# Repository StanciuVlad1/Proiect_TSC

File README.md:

## Stanciu Vlad-Mihai
#### 331CC
<br><br>

OpenBook este un proiect open-source care urmărește să aducă lectura digitală mai aproape de oricine, printr-un dispozitiv accesibil și ușor de reprodus. În cadrul acestui start-up, dezvoltăm un eBook Reader minimalist, construit pe platforma ESP32-C6, echipat cu un ecran e-paper de 7.5 inch, baterie Li-Po, încărcare prin USB-C și butoane fizice pentru navigare.

Dispozitivul este conceput să fie eficient din punct de vedere energetic și intuitiv în utilizare, oferind o interfață simplă bazată pe GPIO, optimizată pentru afișarea de texte și o experiență de e-reading plăcută.

## Cuprins

- [Prezentare Proiect](#prezentare-proiect)
- [Diagramă Bloc](#diagrama-bloc)
- [Lista de Materiale (BOM)](#lista-de-materiale-bom)
- [Funcționalitate Hardware](#functionalitate-hardware)
- [Alocarea Pinilor ESP32-C6](#alocarea-pinilor-esp32-c6)
- [Note de Design](#note-de-design)

## Prezentare Proiect

OpenBook este un cititor de e-bookuri open-source bazat pe microcontrolerul ESP32-C6. Dispozitivul include un display e-paper, stocare pe card SD pentru e-bookuri, o interfață USB-C pentru alimentare și date, și un design compact care se potrivește într-o carcasă personalizată. Scopul este crearea unui e-reader ieftin, modificabil, care poate fi produs în masă, respectând principiile open-source.

Acest repository conține:

- **Hardware**: Fișiere pentru schemă electrică și PCB.
- **Manufacturing**: Fișiere Gerber, Lista de Materiale (BOM) și fișiere Pick and Place.
- **Mechanical**: Modele 3D ale dispozitivului complet (PCB, baterie, display și carcasă).
- **Images**: Randări ale PCB-ului și dispozitivului.

## 🗂️ Diagrama bloc

## Lista de Materiale (BOM)

Tabelul următor listează componentele folosite în designul OpenBook, cu link-uri către furnizori și datasheet-uri.

| Componentă                | Număr Piesă                  | Cantitate | Link Furnizor                                                                 | Link Datasheet                                                                                                                                              | Note                              |
|---------------------------|------------------------------|-----------|--------------------------------------------------------------------------------|-------------------------------------------------------------------------------------------------------------------------------------------------------------|-----------------------------------|
| Senzor mediu              | BME680                       | 1         | [SnapEDA](https://www.snapeda.com/parts/BME680/Bosch/view-part/?welcome=home)   | [Bosch](https://www.bosch-sensortec.com/media/boschsensortec/downloads/datasheets/bst-bme680-ds001.pdf)                                                     | Senzor temperatură, umiditate     |
| Buton tactil              | EVQPUJ02K                    | 3         | [Panasonic](https://industry.panasonic.com/global/en/products/control/switch/light-touch/number/evqpuj02k) | [LCSC](https://www.lcsc.com/datasheet/lcsc_datasheet_2201121800_PANASONIC-EVQPUJ02K_C2936858.pdf)                              | Butoane navigare și pornire       |
| Condensator               | R0402 100K                   | [TBD]     | [ComponentSearch](https://componentsearchengine.com/part-view/R0402%201%25%20100%20K%20(RC0402FR-07100KL)/YAGEO) | [Resistor](https://www.resistor.com/assets/pdf/0402tstd.pdf)                                                                 | Condensator decuplare, SMD 0402   |
| Rezistor                  | R0402 100K                   | [TBD]     | [ComponentSearch](https://componentsearchengine.com/part-view/R0402%201%25%20100%20K%20(RC0402FR-07100KL)/YAGEO) | [Resistor](https://www.resistor.com/assets/pdf/0402tstd.pdf)                                                                 | Rezistor, SMD 0402                |
| Baterie                   | CPH3225A                     | 1         | [SnapEDA](https://www.snapeda.com/parts/CPH3225A/Seiko+Instruments/view-part/?ref=eda) | [Octopart](https://octopart.com/datasheet/cph3225a-seiko-25340571)                                                                  | Baterie Li-Po, ~500mAh            |
| LED                       | KP-1608SURCK                 | 1         | [SnapEDA](https://www.snapeda.com/parts/KP-1608SURCK/Kingbright/view-part/?ref=search&t=LED%200603) | [ELV](https://media.elv.com/file/107153_led_surck1608_data.pdf)                                                                     | LED 0603, indicator               |
| Protecție ESD             | USBLC6-2SC6Y                 | 1         | [SnapEDA](https://www.snapeda.com/parts/USBLC6-2SC6Y/STMicroelectronics/view-part/?ref=eda) | [DigiKey](https://www.digikey.com/en/htmldatasheets/production/1375342/0/0/1/usblc6-2sc6y)                                          | Protecție USB                     |
| Diodă Schottky            | SD0805S020S1R0               | 1         | [Mouser](https://ro.mouser.com/ProductDetail/KYOCERA-AVX/SD0805S020S1R0?qs=jCA%252BPfw4LHbpkAoSnwrdjw%3D%3D) | [AllDataSheet](https://www.alldatasheet.com/view.jsp?Searchword=SD0805S&sField=2)                                                    | Diodă pentru alimentare           |
| Supresor ESD              | PGB1010603MR                | 1         | [SnapEDA](https://www.snapeda.com/parts/PGB1010603MR/Littelfuse/view-part/?ref=eda) | [AllDataSheet](https://www.alldatasheet.com/view.jsp?Searchword=Pgb1010603mr)                                                        | Protecție ESD                     |
| Detector tensiune         | BD5229G-TR                   | 1         | [ComponentSearch](https://componentsearchengine.com/part-view/BD5229G-TR/ROHM%20Semiconductor) | [LCSC](https://www.lcsc.com/datasheet/lcsc_datasheet_2201131330_ROHM-Semicon-BD5229G-TR_C962636.pdf)                         | Monitorizare tensiune             |
| Regulator tensiune        | XC6220A331MR-G               | 1         | [ComponentSearch](https://componentsearchengine.com/part-view/XC6220A331MR-G/Torex) | [AllDataSheet](https://www.alldatasheet.com/view.jsp?Searchword=Xc6220)                                                              | Regulator 3.3V                    |
| Conector USB-C            | USB4110-GF-A                 | 1         | [ComponentSearch](https://componentsearchengine.com/part-view/USB4110-GF-A/GCT%20(GLOBAL%20CONNECTOR%20TECHNOLOGY)) | [GCT](https://gct.co/files/drawings/usb4110.pdf)                                                                            | Interfață USB-C                   |
| LED                       | LEDCHIP-LED0603              | 1         | [Mouser](https://eu.mouser.com/ProductDetail/Adafruit/4208?qs=PzGy0jfpSMtbScLbr0L5dw%3D%3D) | [Arrow](https://www.arrow.com/en/manufacturers/adafruit-industries/datasheets)                                              | LED 0603, Adafruit                |
| Bobină                    | [TBD]                        | 1         | [Comet](https://store.comet.srl.ro/Catalogue/Product/43497/)                           | [Scribd](https://www.scribd.com/document/814581278/Datasheet-Bobina)                                                                | Inductor pentru alimentare        |
| Siguranță resetabilă      | PFMF                          | 1         | [Mouser](https://www.mouser.co.uk/ProductDetail/EPCOS-TDK/B72520T0350K062?qs=dEfas%2FXlABIszF52uu7vrg%3D%3D) | [Mouser](https://ro.mouser.com/c/ds/circuit-protection/thermistors/resettable-fuses-pptc/?m=Schurter&series=PFMF)             | Protecție circuit                 |
| MOSFET                    | DMG2305UX-7                  | 1         | [ComponentSearch](https://componentsearchengine.com/part-view/DMG2305UX-7/Diodes%20Incorporated) | [Mouser](https://www.mouser.com/datasheet/2/115/DMG2305UX-266242.pdf)                                                       | Comutare putere                   |
| MOSFET                    | Si1308EDL-T1-GE3             | 1         | [ComponentSearch](https://componentsearchengine.com/part-view/SI1308EDL-T1-GE3/Vishay) | [AllDataSheet](https://www.alldatasheet.com/view.jsp?Searchword=Si1308edl)                                                   | Comutare putere                   |
| IC management baterie     | MCP73831T-5ACI/OT            | 1         | [Mouser](https://www.mouser.co.uk/ProductDetail/Microchip-Technology/MCP73831T-5ACI-OT?qs=hH%252BOa0VZEiAcgAcEkuamXg%3D%3D) | [Microchip](https://ww1.microchip.com/downloads/en/DeviceDoc/MCP73831-Family-Data-Sheet-DS20001984H.pdf)                     | Încărcare baterie                 |
| Lipire SMD                | SMD Solder                   | [TBD]     | [GrabCAD](https://grabcad.com/library/solder-jumpers-1)                                | -                                                                                                                                                           | Pentru asamblare SMD              |
| Memorie flash             | W25Q512JVEIQ                 | 1         | [SnapEDA](https://www.snapeda.com/parts/W25Q512JVEIQ/Winbond+Electronics/view-part/) | [Mouser](https://www.mouser.com/datasheet/2/949/W25Q512JV_SPI_RevB_06252019_KMS-2487502.pdf)                                | Memorie SPI                       |
| Modul microcontroler      | ESP32-C6-WROOM-1-N8          | 1         | [SnapEDA](https://www.snapeda.com/parts/ESP32-C6-WROOM-1-N8/Espressif+Systems/view-part/?ref=eda) | [Mouser](https://www.mouser.com/catalog/specsheets/Espressif_ESP32_C6_WROOM_1%20_Datasheet_V0.1_PRELIMINARY_en.pdf)         | Modul Wi-Fi/Bluetooth             |
| Ceas timp real            | DS3231SN#                    | 1         | [SnapEDA](https://www.snapeda.com/parts/DS3231SN%23/Analog+Devices/view-part/?ref=eda) | [AllDataSheet](https://www.alldatasheet.com/view.jsp?Searchword=Ds3231sn%20datasheet)                                        | RTC pentru timp                   |
| Monitor baterie           | MAX17048G+T10                | 1         | [SnapEDA](https://www.snapeda.com/parts/MAX17048G+T10/Analog+Devices/view-part/?ref=eda) | [AllDataSheet](https://www.alldatasheet.com/view.jsp?Searchword=Max17048)                                                    | Monitorizare nivel baterie        |

## Funcționalitate Hardware

Hardware-ul OpenBook este proiectat pentru a echilibra costul, eficiența energetică și funcționalitatea. Caracteristicile principale includ:

- **Microcontroler ESP32-C6**:
  - **Nucleu**: Procesor RISC-V single-core.
  - **Conectivitate**: Wi-Fi 6 și Bluetooth 5 pentru actualizări de firmware sau integrare cloud.
  - **Interfețe**: SPI pentru display și card SD, GPIO pentru butoane, USB pentru alimentare și depanare.
  - **Consum de energie**: Optimizat pentru funcționare cu consum redus, cu moduri de sleep pentru a prelungi durata bateriei.

- **Display E-Paper**:
  - Display e-paper de 2.13" (rezoluție [TBD, ex. 250x122 pixeli]).
  - Conectat prin SPI pentru actualizare rapidă și consum redus.
  - Ideal pentru citit în diverse condiții de iluminare, cu consum minim.

- **Modul Card SD**:
  - Stochează e-bookuri și alte fișiere media.
  - Conectat prin SPI pentru transfer de date fiabil.
  - Suportă carduri microSD standard.

- **Interfață USB-C**:
  - Furnizează alimentare (intrare 5V) și încarcă bateria prin IC-ul de management al puterii.
  - Suportă transfer de date pentru depanare sau actualizări de firmware.

- **Baterie și Management Putere**:
  - Baterie Li-Po de 3.7V (~500mAh, capacitate exactă [TBD]).
  - IC de management al puterii (ex. TP4056) gestionează încărcarea și reglarea tensiunii (3.3V pentru ESP32 și alte componente).
  - Durata estimată a bateriei: [TBD, ex. 20 ore de citire activă], bazată pe calcule pentru actualizarea display-ului, modurile sleep ale ESP32 și accesul la cardul SD.

- **Butoane**:
  - Trei butoane tactile pentru navigare (următoarea/pagina anterioară) și pornire/meniu.
  - Conectate la pinii GPIO ai ESP32 cu rezistoare pull-up.

- **Calcule Consum Energie**:
  - ESP32-C6 (activ): ~100mA la 3.3V.
  - Display E-Paper (actualizare): ~10mA pentru 1s per pagină.
  - Card SD (citire): ~50mA în timpul accesului.
  - Consum total activ: [TBD, ex. ~150mA mediu].
  - Mod sleep: [TBD, ex. <1mA].

*(Notă: Actualizează consumul de energie și alte specificații pe baza alegerilor tale de design și a datasheet-urilor.)*

## Alocarea Pinilor ESP32-C6

Pinii ESP32-C6 sunt alocați astfel:

| Pin       | Funcție                 | Componentă/Modul        | Note                              |
|-----------|-------------------------|-------------------------|-----------------------------------|
| GPIO0     | SPI MOSI                | Display E-Paper, Card SD| Bus SPI comun                     |
| GPIO1     | SPI MISO                | Display E-Paper, Card SD| Bus SPI comun                     |
| GPIO2     | SPI SCK                 | Display E-Paper, Card SD| Bus SPI comun                     |
| GPIO3     | SPI CS (Display)        | Display E-Paper         | Selectare cip pentru display      |
| GPIO4     | SPI CS (Card SD)        | Modul Card SD           | Selectare cip pentru card SD      |
| GPIO5     | Buton 1 (Pagina Urm.)   | Buton Tactil            | Pull-up, activ low                |
| GPIO6     | Buton 2 (Pagina Ant.)   | Buton Tactil            | Pull-up, activ low                |
| GPIO7     | Buton 3 (Pornire/Meniu) | Buton Tactil            | Pull-up, activ low                |
| GPIO8     | Reset Display           | Display E-Paper         | Activ low                         |
| GPIO9     | Busy Display            | Display E-Paper         | Intrare de la display             |
| VBUS      | Alimentare USB          | Conector USB-C          | Intrare 5V                        |
| 3V3       | Linie Alimentare        | Toate componentele      | Reglat din baterie/USB            |

*(Notă: Verifică alocarea pinilor față de schemă. Actualizează tabelul cu numerele exacte ale pinilor și funcțiile pe baza designului tău.)*

### De ce acești pini?

- **Pini SPI (GPIO0-4)**: Aleși pentru suportul hardware dedicat SPI, asigurând comunicație rapidă și fiabilă cu display-ul și cardul SD. Un bus SPI comun minimizează utilizarea pinilor.
- **Pini Butoane (GPIO5-7)**: Selectați pentru capabilitățile de intrare generală și suport pentru întreruperi, permițând interacțiune rapidă cu utilizatorul.
- **Pini Control Display (GPIO8-9)**: Folosiți pentru semnalele de reset și busy, conform cerințelor datasheet-ului display-ului e-paper.
- **Pini Alimentare (VBUS, 3V3)**: Standard pentru livrarea și reglarea energiei.

## Note de Design

- **Schemă și Design PCB**:
  - Schema (`Hardware/openbook.sch`) respectă referința furnizată.
  - Layout-ul PCB (`Hardware/openbook.brd`) respectă constrângerile mecanice, cu toate componentele pe stratul TOP și rutarea pe ambele straturi TOP și BOTTOM.
  - Traseele de alimentare folosesc lățimea de 0.3mm, iar traseele de semnal au lățimea minimă de 0.15mm, conform ghidului.
  - Antena ESP32-C6 este poziționată la marginea PCB-ului, cu o decupare dedesubt pentru a minimiza interferențele.

- **Design Mecanic**:
  - Modelul 3D (`Mechanical/openbook.step`) include PCB-ul, bateria, display-ul e-paper și carcasa modificată.
  - Bateria se conectează direct la pad-uri de test (fără conector JST) pentru a economisi spațiu.

## 🔧 Provocări și decizii tehnice

- **Erori DRC**  
  Au fost ignorate erorile de tip *"Only INPUT pins on NET ID"* și cele legate de dimensiunile butoanelor și conectorului USB, în conformitate cu ghidul de proiectare, deoarece nu afectează funcționarea corectă a dispozitivului.

- **Amplasarea componentelor**  
  Componentele au fost plasate strategic în jurul ESP32 și al driverului e-paper pentru a reduce lungimea traseelor și a asigura o bună integritate a semnalului.

- **Via Stitching**  
  A fost implementat între planele de masă TOP și BOTTOM, în special în proximitatea ESP32, pentru a îmbunătăți performanța EMI și stabilitatea generală.

- **Silkscreen**  
  Au fost incluse doar denumirile componentelor, fără valorile acestora, pentru a păstra lizibilitatea și a respecta bunele practici în designul PCB-urilor.

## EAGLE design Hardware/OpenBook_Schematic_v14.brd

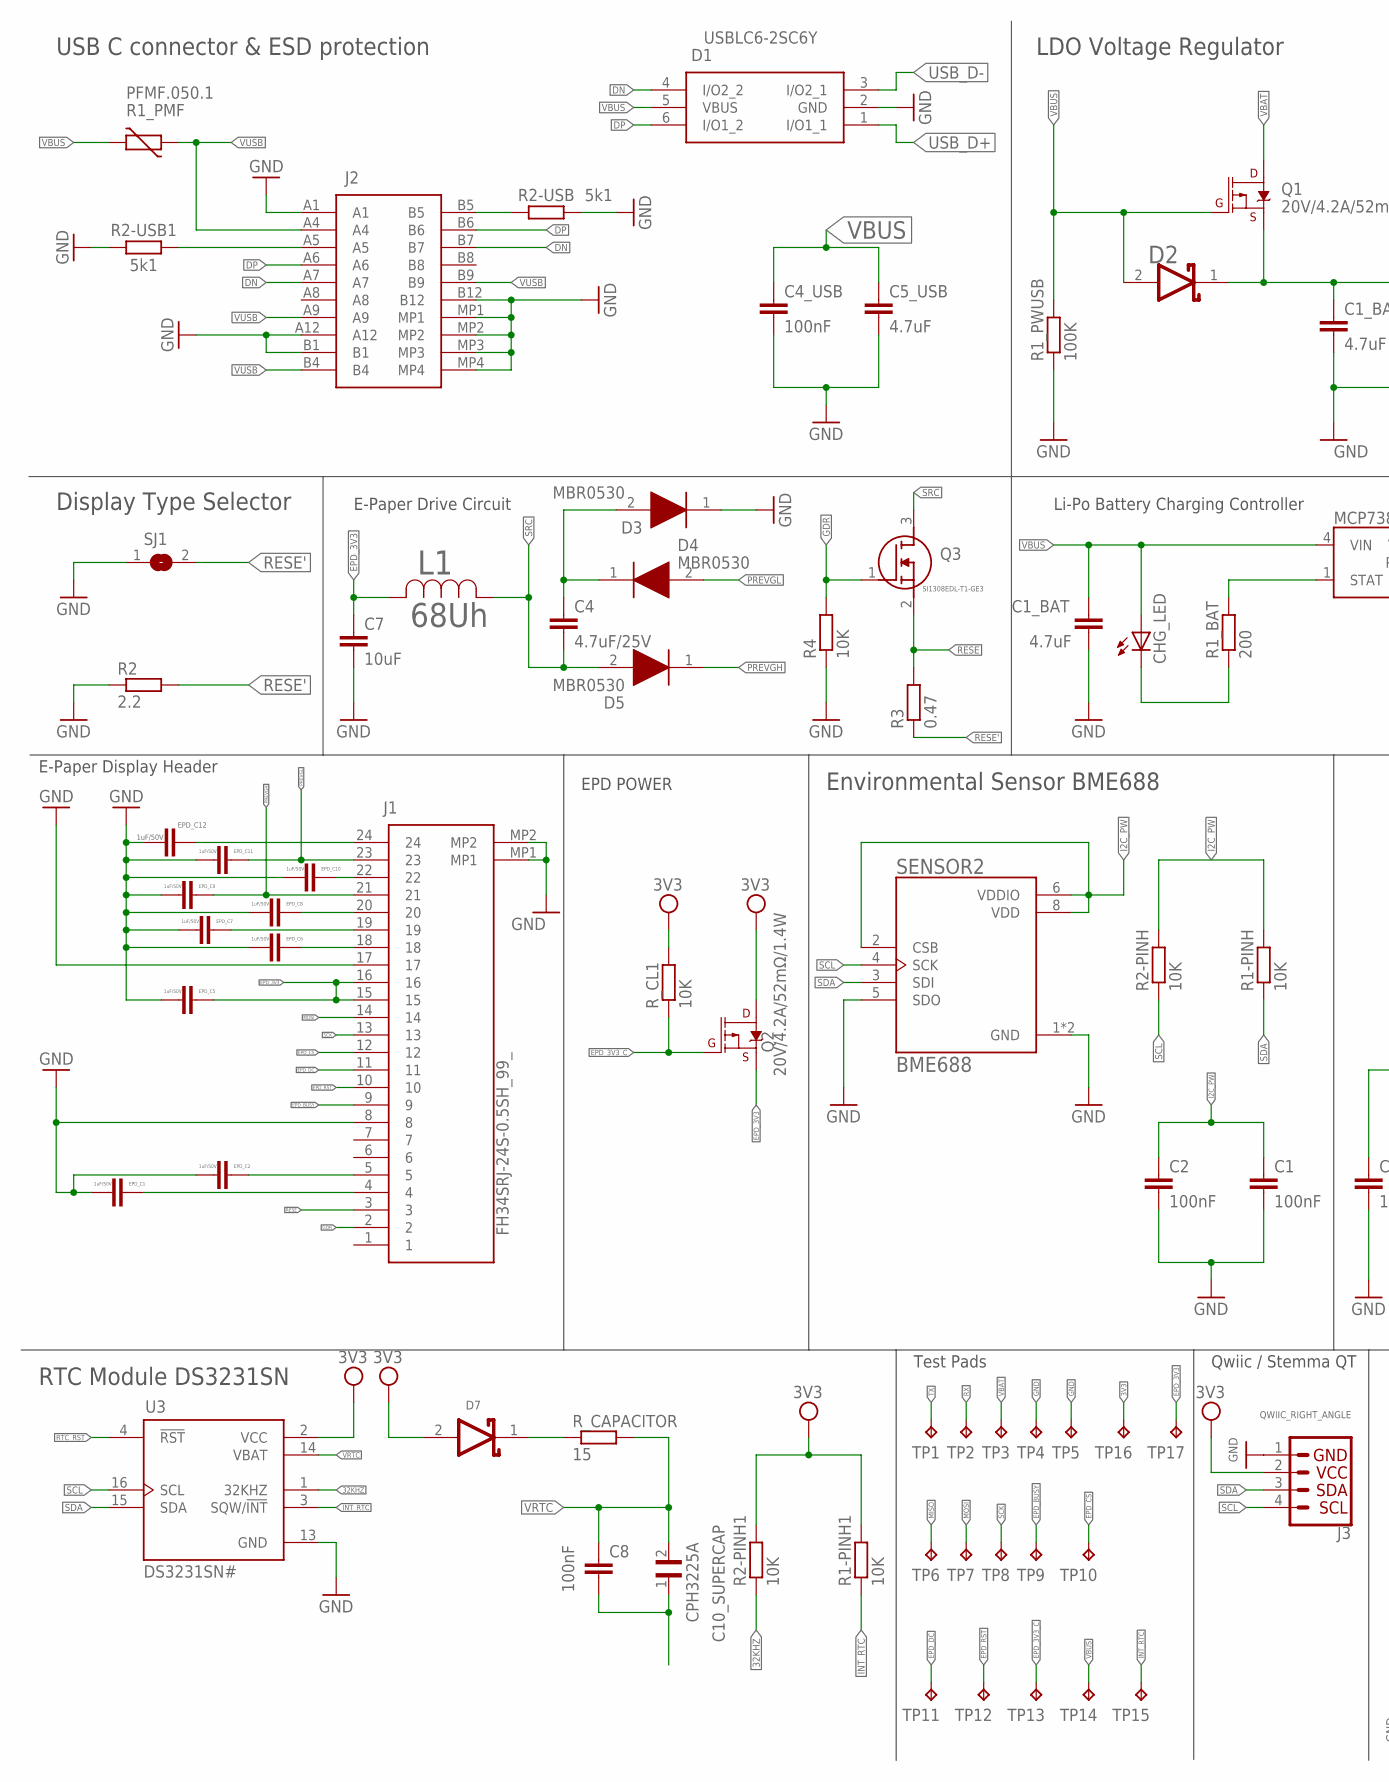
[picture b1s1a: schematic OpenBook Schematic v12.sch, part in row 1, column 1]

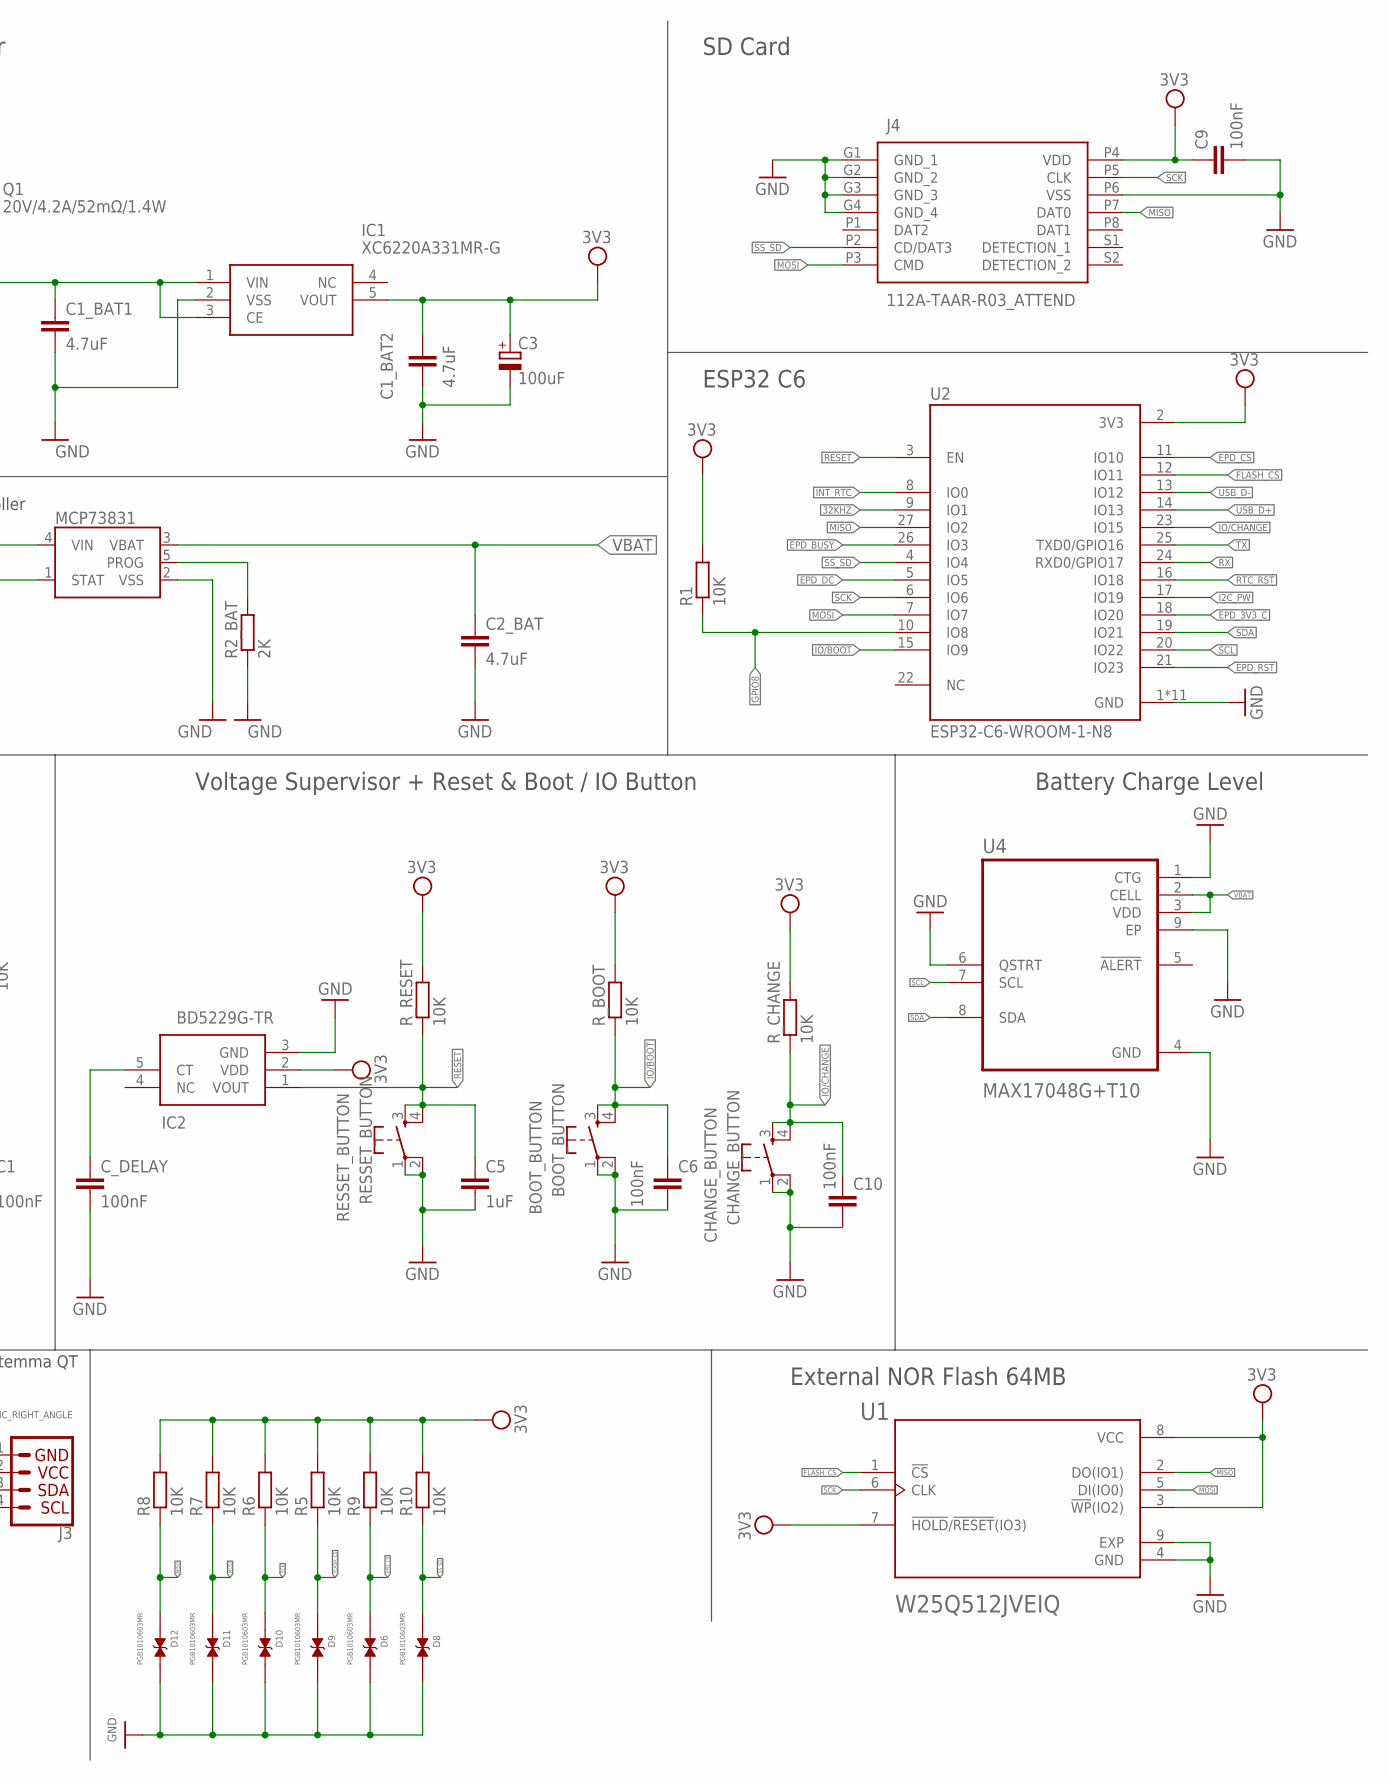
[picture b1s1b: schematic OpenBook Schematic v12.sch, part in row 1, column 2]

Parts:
BOOT_BUTTON: BOOT_BUTTON; MYBUTTON
C1, C2, C4_USB, C6, C8, C9, C10: 100nF; EAGLE-LTSPICE_C0402
C1_BAT, C1_BAT1, C1_BAT2, C2_BAT, C5_USB: 4.7uF; EAGLE-LTSPICE_C0402
C3: 100uF; RCL_CT3528
C4: 4.7uF/25V; EAGLE-LTSPICE_C0402
C5: 1uF; EAGLE-LTSPICE_C0402
C7: 10uF; EAGLE-LTSPICE_C0402
C10_SUPERCAP: CPH3225A; CAPCP3225X100N
CHANGE_BUTTON: CHANGE_BUTTON; MYBUTTON
CHG_LED: ADAFRUIT_LEDCHIP-LED0603; ADAFRUIT_CHIP-LED0603
C_DELAY: 100nF; EAGLE-LTSPICE_C0402
D1: USBLC6-2SC6Y; SOT95P280X145-6N
D2, D7: ESP32_WROVER_AVX---SD0805S020S1R0_AVX_SD0805S020S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; ESP32_WROVER_AVX---SD0805S020S1R0_AVX_SD0805S020S1R0_0
D3, D4, D5: MBR0530; SOD3716X135N
D6, D8, D9, D10, D11, D12: PGB1010603MR; DIOC1608X36N
EPD_C1, EPD_C2, EPD_C5, EPD_C6, EPD_C7, EPD_C8, EPD_C9, EPD_C10, EPD_C11, EPD_C12: 1uF/50V; EAGLE-LTSPICE_C0402
IC1: XC6220A331MR-G; SOT95P280X120-5N
IC2: BD5229G-TR; SOT95P280X125-5N
J1: FH34SRJ-24S-0.5SH_99_; FH34SRJ24S05SH99
J2: SAMACSYS_PARTS_USB4110-GF-A; SAMACSYS_PARTS_USB4110GFA
J3: QWIIC_RIGHT_ANGLE; JST04_1MM_RA
J4: 112A-TAAR-R03_ATTEND; 112ATAARR03ATTEND
L1: 68Uh; IND_4828-WE-TPC_WRE
MCP73831: ESP32_WROVER_SPARKFUN-IC-POWER_MCP73831; ESP32_WROVER_SPARKFUN-IC-POWER_SOT23-5
Q1, Q2: 20V/4.2A/52mΩ/1.4W; ESP32_WROVER_SPARKFUN-DISCRETESEMI_SOT23-3
Q3: SI1308EDL-T1-GE3; SOT65P210X110-3N
R1, R1-PINH, R1-PINH1, R2-PINH, R2-PINH1, R4, R5, R6, R7, R8, R9, R10: 10K; ESP32_WROVER_EAGLE-LTSPICE_R0402
R1_BAT: 200; ESP32_WROVER_EAGLE-LTSPICE_R0402
R1_PMF: PFMF.050.1; ESP32C6_VARISTOR_CT/CN1812
R1_PWUSB: 100K; ESP32_WROVER_EAGLE-LTSPICE_R0402
R2: 2.2; ESP32_WROVER_EAGLE-LTSPICE_R0402
R2-USB, R2-USB1: 5k1; RESC1005X40
R2_BAT: 2K; ESP32_WROVER_EAGLE-LTSPICE_R0402
R3: 0.47; ESP32_WROVER_EAGLE-LTSPICE_R0402
RESSET_BUTTON: RESSET_BUTTON; MYBUTTON
R_BOOT: 10K; ESP32_WROVER_EAGLE-LTSPICE_R0402
R_CAPACITOR: 15; ESP32_WROVER_EAGLE-LTSPICE_R0402
R_CHANGE: 10K; ESP32_WROVER_EAGLE-LTSPICE_R0402
R_CL1: 10K; ESP32_WROVER_EAGLE-LTSPICE_R0402
R_RESET: 10K; ESP32_WROVER_EAGLE-LTSPICE_R0402
SENSOR2: BME688; ESP32_WROVER_BME680_PSON80P300X300X100-8N
SJ1: SJ
TP1, TP2, TP3, TP4, TP5, TP6, TP7, TP8, TP9, TP10, TP11, TP12, TP13, TP14, TP15, TP16, TP17: TPTP20R; TP20R
U1: W25Q512JVEIQ; SON127P600X800X80-9N
U2: ESP32-C6-WROOM-1-N8; XCVR_ESP32-C6-WROOM-1-N8
U3: DS3231SN#; SOIC127P1032X265-16N
U4: MAX17048G+T10; SON50P200X200X80-9N

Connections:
3V3: C1_BAT2.1, C3.+, C9.1, D7.2 (ANODE), IC1.5 (VOUT), IC2.2 (VDD), J3.2, J4.P4 (VDD), Q2.3 (D), R1.2, R1-PINH1.2, R2-PINH1.2, R5.2, R6.2, R7.2, R8.2, R9.2, R10.2, R_BOOT.2, R_CHANGE.2, R_CL1.2, R_RESET.2, TP16.TP, U1.3 (!WP!(IO2)), U1.7 (!HOLD!/!RESET!(IO3)), U1.8 (VCC), U2.2 (3V3), U3.2 (VCC)
32KHZ: R2-PINH1.1, U2.9 (IO1), U3.1 (32KHZ)
DN: D1.4 (I/O2_2), J2.A7, J2.B7
DP: D1.6 (I/O1_2), J2.A6, J2.B6
EPD_3V3: C7.1, EPD_C5.1, J1.15, J1.16, L1.2, Q2.2 (S), TP17.TP
EPD_3V3_C: Q2.1 (G), R_CL1.1, TP13.TP, U2.18 (IO20)
EPD_BUSY: J1.9, TP9.TP, U2.26 (IO3)
EPD_CS: D6.2, J1.12, R9.1, TP10.TP, U2.11 (IO10)
EPD_DC: J1.11, TP11.TP, U2.5 (IO5)
EPD_RST: J1.10, TP12.TP, U2.21 (IO23)
FLASH_CS: D9.2, R5.1, U1.1 (!CS), U2.12 (IO11)
GDR: J1.2, Q3.1 (G), R4.2
GND: BOOT_BUTTON.1, BOOT_BUTTON.2, C1.2, C1_BAT.2, C1_BAT1.2, C1_BAT2.2, C2.2, C2_BAT.2, C3.-, C4_USB.2, C5.2, C5_USB.2, C6.2, C7.2, C9.2, C10.2, CHANGE_BUTTON.1, CHANGE_BUTTON.2, C_DELAY.2, D1.2 (GND), D3.1 (K), D6.1, D8.1, D9.1, D10.1, D11.1, D12.1, EPD_C1.2, EPD_C2.2, EPD_C5.2, EPD_C6.2, EPD_C7.2, EPD_C8.2, EPD_C9.2, EPD_C10.2, EPD_C11.2, EPD_C12.2, IC1.2 (VSS), IC2.3 (GND), J1.8, J1.17, J1.MP1, J1.MP2, J2.A1, J2.A12, J2.B1, J2.B12, J2.MP1, J2.MP2, J2.MP3, J2.MP4, J3.1, J4.G1 (GND_1), J4.G2 (GND_2), J4.G3 (GND_3), J4.G4 (GND_4), J4.P6 (VSS), MCP73831.2 (VSS), R1_PWUSB.1, R2.1, R2-USB.2, R2-USB1.1, R2_BAT.1, R4.1, RESSET_BUTTON.1, RESSET_BUTTON.2, SENSOR2.1 (GND), SENSOR2.5 (SDO), SENSOR2.7 (GND), SJ1.1, TP4.TP, TP5.TP, U1.4 (GND), U1.9 (EXP), U2.1 (GND), U2.28 (GND), U2.29_1 (GND), U2.29_2 (GND), U2.29_3 (GND), U2.29_4 (GND), U2.29_5 (GND), U2.29_6 (GND), U2.29_7 (GND), U2.29_8 (GND), U2.29_9 (GND), U3.13 (GND), U4.1 (CTG), U4.4 (GND), U4.6 (QSTRT), U4.9 (EP)
GPIO8: R1.1, U2.10 (IO8)
I2C_PW: C1.1, C2.1, SENSOR2.2 (CSB), SENSOR2.6 (VDDIO), SENSOR2.8 (VDD), U2.17 (IO19)
INT_RTC: R1-PINH1.1, TP15.TP, U2.8 (IO0), U3.3 (SQW/!INT)
IO/BOOT: BOOT_BUTTON.3, BOOT_BUTTON.4, C6.1, R_BOOT.1, U2.15 (IO9)
IO/CHANGE: C10.1, CHANGE_BUTTON.3, CHANGE_BUTTON.4, R_CHANGE.1, U2.23 (IO15)
MISO: D12.2, J4.P7 (DAT0), R8.1, TP6.TP, U1.2 (DO(IO1)), U2.27 (IO2)
MOSI: D11.2, J1.14, J4.P3 (CMD), R7.1, TP7.TP, U1.5 (DI(IO0)), U2.7 (IO7)
unnamed: C1_BAT1.1, D2.1 (CATHODE), IC1.1 (VIN), IC1.3 (CE), Q1.2 (S)
unnamed: J2.A5, R2-USB1.2
unnamed: J2.B5, R2-USB.1
unnamed: EPD_C12.1, J1.24
unnamed: C4.1, D3.2 (A), D4.1 (K)
unnamed: CHG_LED.C, R1_BAT.1
unnamed: MCP73831.1 (STAT), R1_BAT.2
unnamed: R1-PINH.2, R2-PINH.2
unnamed: MCP73831.5 (PROG), R2_BAT.2
unnamed: C_DELAY.1, IC2.5 (CT)
unnamed: D7.1 (CATHODE), R_CAPACITOR.1
unnamed: C8.2, C10_SUPERCAP.1
unnamed: EPD_C10.1, J1.22
unnamed: EPD_C8.1, J1.20
unnamed: EPD_C7.1, J1.19
unnamed: EPD_C6.1, J1.18
unnamed: EPD_C2.1, J1.5
unnamed: EPD_C1.1, J1.4
PREVGH: D5.1 (K), EPD_C9.1, J1.21
PREVGL: D4.2 (A), EPD_C11.1, J1.23
RESE: J1.3, Q3.2 (S), R3.2
RESE': R2.2, R3.1, SJ1.2
RESET: C5.1, IC2.1 (VOUT), RESSET_BUTTON.3, RESSET_BUTTON.4, R_RESET.1, U2.3 (EN)
RTC_RST: U2.16 (IO18), U3.4 (!RST)
RX: TP2.TP, U2.24 (RXD0/GPIO17)
SCK: D10.2, J1.13, J4.P5 (CLK), R6.1, TP8.TP, U1.6 (CLK), U2.6 (IO6)
SCL: J3.4, R2-PINH.1, SENSOR2.4 (SCK), U2.20 (IO22), U3.16 (SCL), U4.7 (SCL)
SDA: J3.3, R1-PINH.1, SENSOR2.3 (SDI), U2.19 (IO21), U3.15 (SDA), U4.8 (SDA)
SRC: C4.2, D5.2 (A), L1.1, Q3.3 (D)
SS_SD: D8.2, J4.P2 (CD/DAT3), R10.1, U2.4 (IO4)
TX: TP1.TP, U2.25 (TXD0/GPIO16)
USB_D+: D1.1 (I/O1_1), U2.14 (IO13)
USB_D-: D1.3 (I/O2_1), U2.13 (IO12)
VBAT: C2_BAT.1, MCP73831.3 (VBAT), Q1.3 (D), TP3.TP, U4.2 (CELL), U4.3 (VDD)
VBUS: C1_BAT.1, C4_USB.1, C5_USB.1, CHG_LED.A, D1.5 (VBUS), D2.2 (ANODE), MCP73831.4 (VIN), Q1.1 (G), R1_PMF.2, R1_PWUSB.2, TP14.TP
VRTC: C8.1, C10_SUPERCAP.2, R_CAPACITOR.2, U3.14 (VBAT)
VUSB: J2.A4, J2.A9, J2.B4, J2.B9, R1_PMF.1

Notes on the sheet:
USB C connector & ESD protection
SD Card
LDO Voltage Regulator
ESP32 C6
Display Type Selector
E-Paper Drive Circuit
Li-Po Battery Charging Controller
E-Paper Display Header
EPD POWER
Environmental Sensor BME688
Voltage Supervisor + Reset & Boot / IO Button
Battery Charge Level
RTC Module DS3231SN
Test Pads
Qwiic / Stemma QT
External NOR Flash 64MB

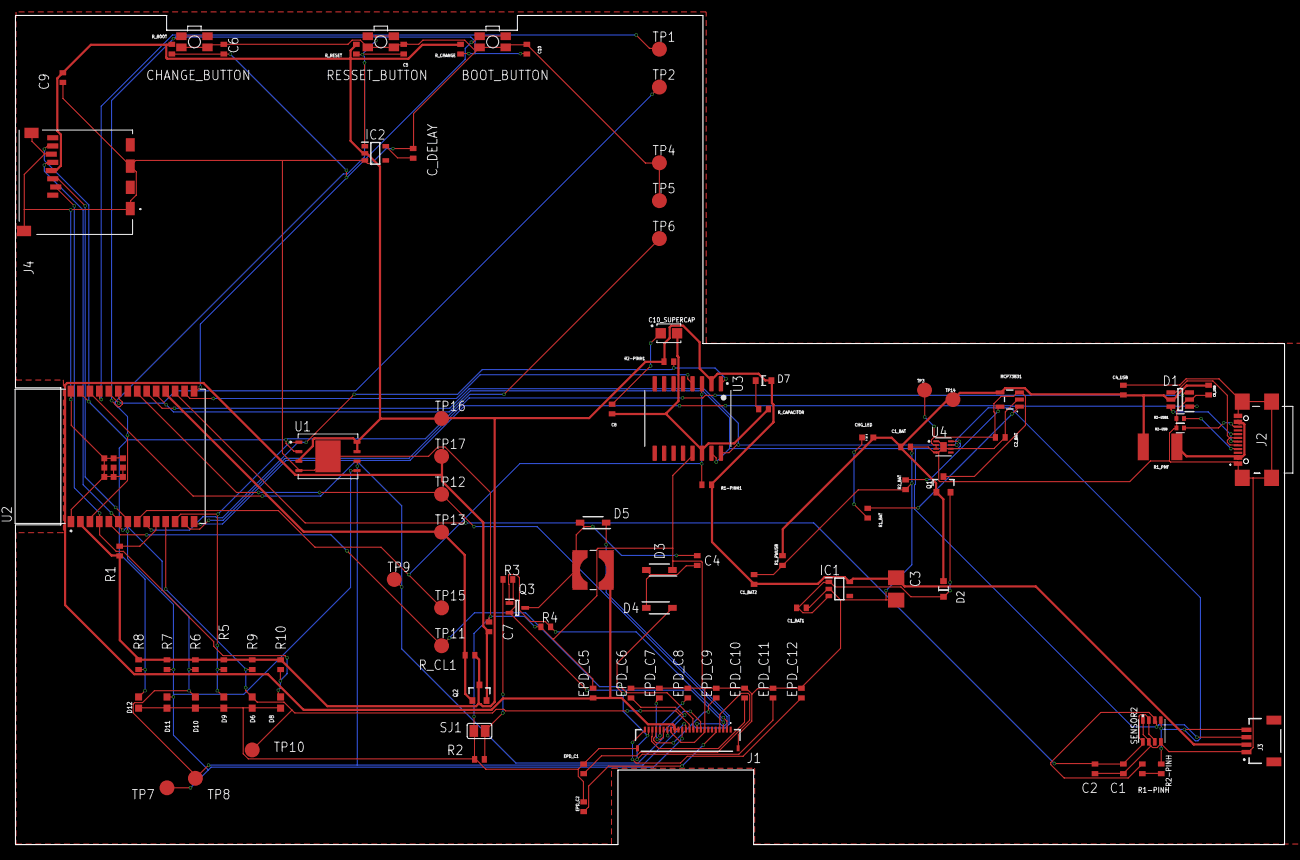
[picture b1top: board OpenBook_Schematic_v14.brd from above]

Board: 2 copper layers, 170.2 x 111.2 mm, 103 parts (0 on the bottom side), 57 nets.

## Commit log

2025-04-06 Pushing Mechanical and Hardware
2025-04-06 Uploading images
2025-04-06 Adding part of manufacturing
2025-04-06 Removing useless files and adding Bill Of Materials
2025-04-06 Create LICENSE

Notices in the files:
parts and their libraries:
DeskAssistant v19 v1.flbr: COPYRIGHT: Copyright (C) 2024 Ultra Librarian. All rights reserved.
